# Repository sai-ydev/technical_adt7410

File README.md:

# ADT74x0 Technical Challenge

This repository contains the Python driver and the hardware design files meant for a take-home assignment offered by an organization. 

## Task Briefing

Your task is to create a thermostat that will also log temperature with a 10sec period. We've already chosen to integrate this into the Raspberry Pi CM4 system we are using, and to use the AD7414 temperature sensor chip. You are expected to create the electrical interface from the AD7414 to the Raspberry Pi and write the little bit of software to drive it.

The schematic has been started, and is provided for you as a kicad file, but really this is an exercise so feel completely free to return your answer as pen drawn on the PDF if that's easier. The pins GPIO0-GPIO13 are available to you, but I2C bus 0 has some devices on it already so do not use it so as to avoid contention for the bus. To the schematic, add 2 Watts of switchable heat, using a heating element of your choice. Make sure to specify it properly, either a part number if you're using something off the shelf, or construction details if making one from scratch. The heating element can be either board-mounted or attached by wires.

Write enough Python software to use this as a thermostat that can keep the temperature above a set point as well as log the temperature averaged over the last ten seconds, every ten seconds. Target Python 3.6 and write against the following API for board support.

## My Submission
 I used an ADT7420 temperature sensor. This was because AD7414 were generally not available from major distributors and I approached this problem as if I were actually designing a PCB for a real-life project. This repository includes the python drivers. 
 
 * `adt7420.py` - Drivers for the ADT7420 Temperature Sensor
 * `thermostat.py` - Thermostat class for interfacing temperature sensor and turn on heater

## Hardware

The Eagle PCB schematic and layout files are available in the `hardware` folder. It also includes a BOM file and Gerber files.

## Sources
1. My STM32 drivers for ADT7410 - [Link](https://github.com/sai-ydev/adt7410)
2. Analog ADT74x0 driver - [Link](https://github.com/analogdevicesinc/EVAL-ADICUP360/tree/master/projects/ADuCM360_demo_adt7420_pmdz)

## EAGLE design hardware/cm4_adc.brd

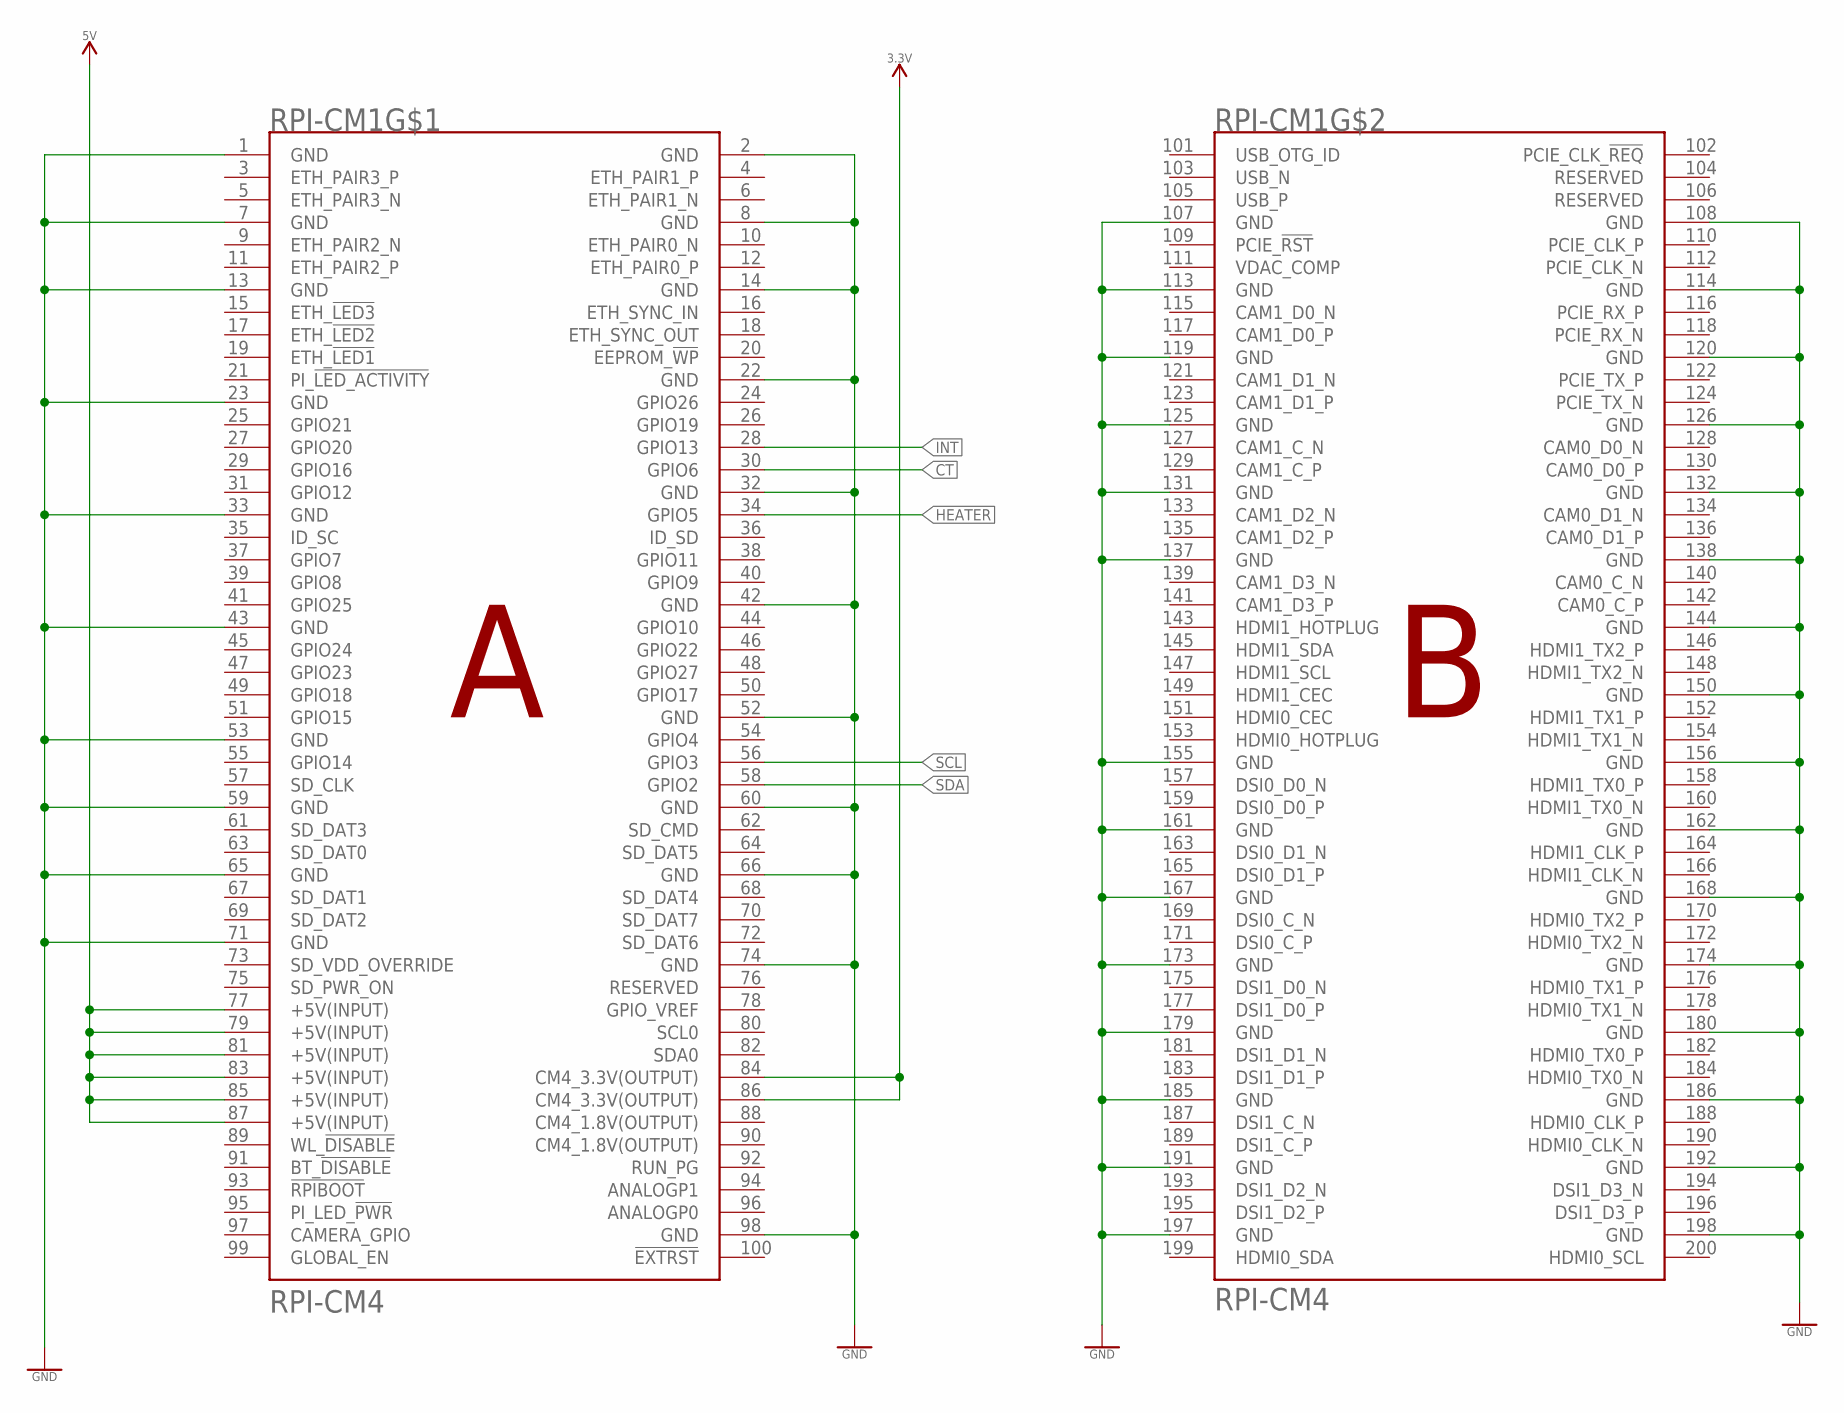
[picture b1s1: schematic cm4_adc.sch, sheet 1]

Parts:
RPI-CM1: RPI-CM4

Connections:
3.3V: RPI-CM1.84 (CM4_3.3V(OUTPUT)), RPI-CM1.86 (CM4_3.3V(OUTPUT)); also elsewhere on the board
5V: RPI-CM1.77 (+5V(INPUT)), RPI-CM1.79 (+5V(INPUT)), RPI-CM1.81 (+5V(INPUT)), RPI-CM1.83 (+5V(INPUT)), RPI-CM1.85 (+5V(INPUT)), RPI-CM1.87 (+5V(INPUT)); also elsewhere on the board
CT: RPI-CM1.30 (GPIO6); also elsewhere on the board
GND: RPI-CM1.1 (GND), RPI-CM1.2 (GND), RPI-CM1.7 (GND), RPI-CM1.8 (GND), RPI-CM1.13 (GND), RPI-CM1.14 (GND), RPI-CM1.22 (GND), RPI-CM1.23 (GND), RPI-CM1.32 (GND), RPI-CM1.33 (GND), RPI-CM1.42 (GND), RPI-CM1.43 (GND), RPI-CM1.52 (GND), RPI-CM1.53 (GND), RPI-CM1.59 (GND), RPI-CM1.60 (GND), RPI-CM1.65 (GND), RPI-CM1.66 (GND), RPI-CM1.71 (GND), RPI-CM1.74 (GND), RPI-CM1.98 (GND), RPI-CM1.107 (GND), RPI-CM1.108 (GND), RPI-CM1.113 (GND), RPI-CM1.114 (GND), RPI-CM1.119 (GND), RPI-CM1.120 (GND), RPI-CM1.125 (GND), RPI-CM1.126 (GND), RPI-CM1.131 (GND), RPI-CM1.132 (GND), RPI-CM1.137 (GND), RPI-CM1.138 (GND), RPI-CM1.144 (GND), RPI-CM1.150 (GND), RPI-CM1.155 (GND), RPI-CM1.156 (GND), RPI-CM1.161 (GND), RPI-CM1.162 (GND), RPI-CM1.167 (GND), RPI-CM1.168 (GND), RPI-CM1.173 (GND), RPI-CM1.174 (GND), RPI-CM1.179 (GND), RPI-CM1.180 (GND), RPI-CM1.185 (GND), RPI-CM1.186 (GND), RPI-CM1.191 (GND), RPI-CM1.192 (GND), RPI-CM1.197 (GND), RPI-CM1.198 (GND); also elsewhere on the board
HEATER: RPI-CM1.34 (GPIO5); also elsewhere on the board
INT: RPI-CM1.28 (GPIO13); also elsewhere on the board
SCL: RPI-CM1.56 (GPIO3); also elsewhere on the board
SDA: RPI-CM1.58 (GPIO2); also elsewhere on the board

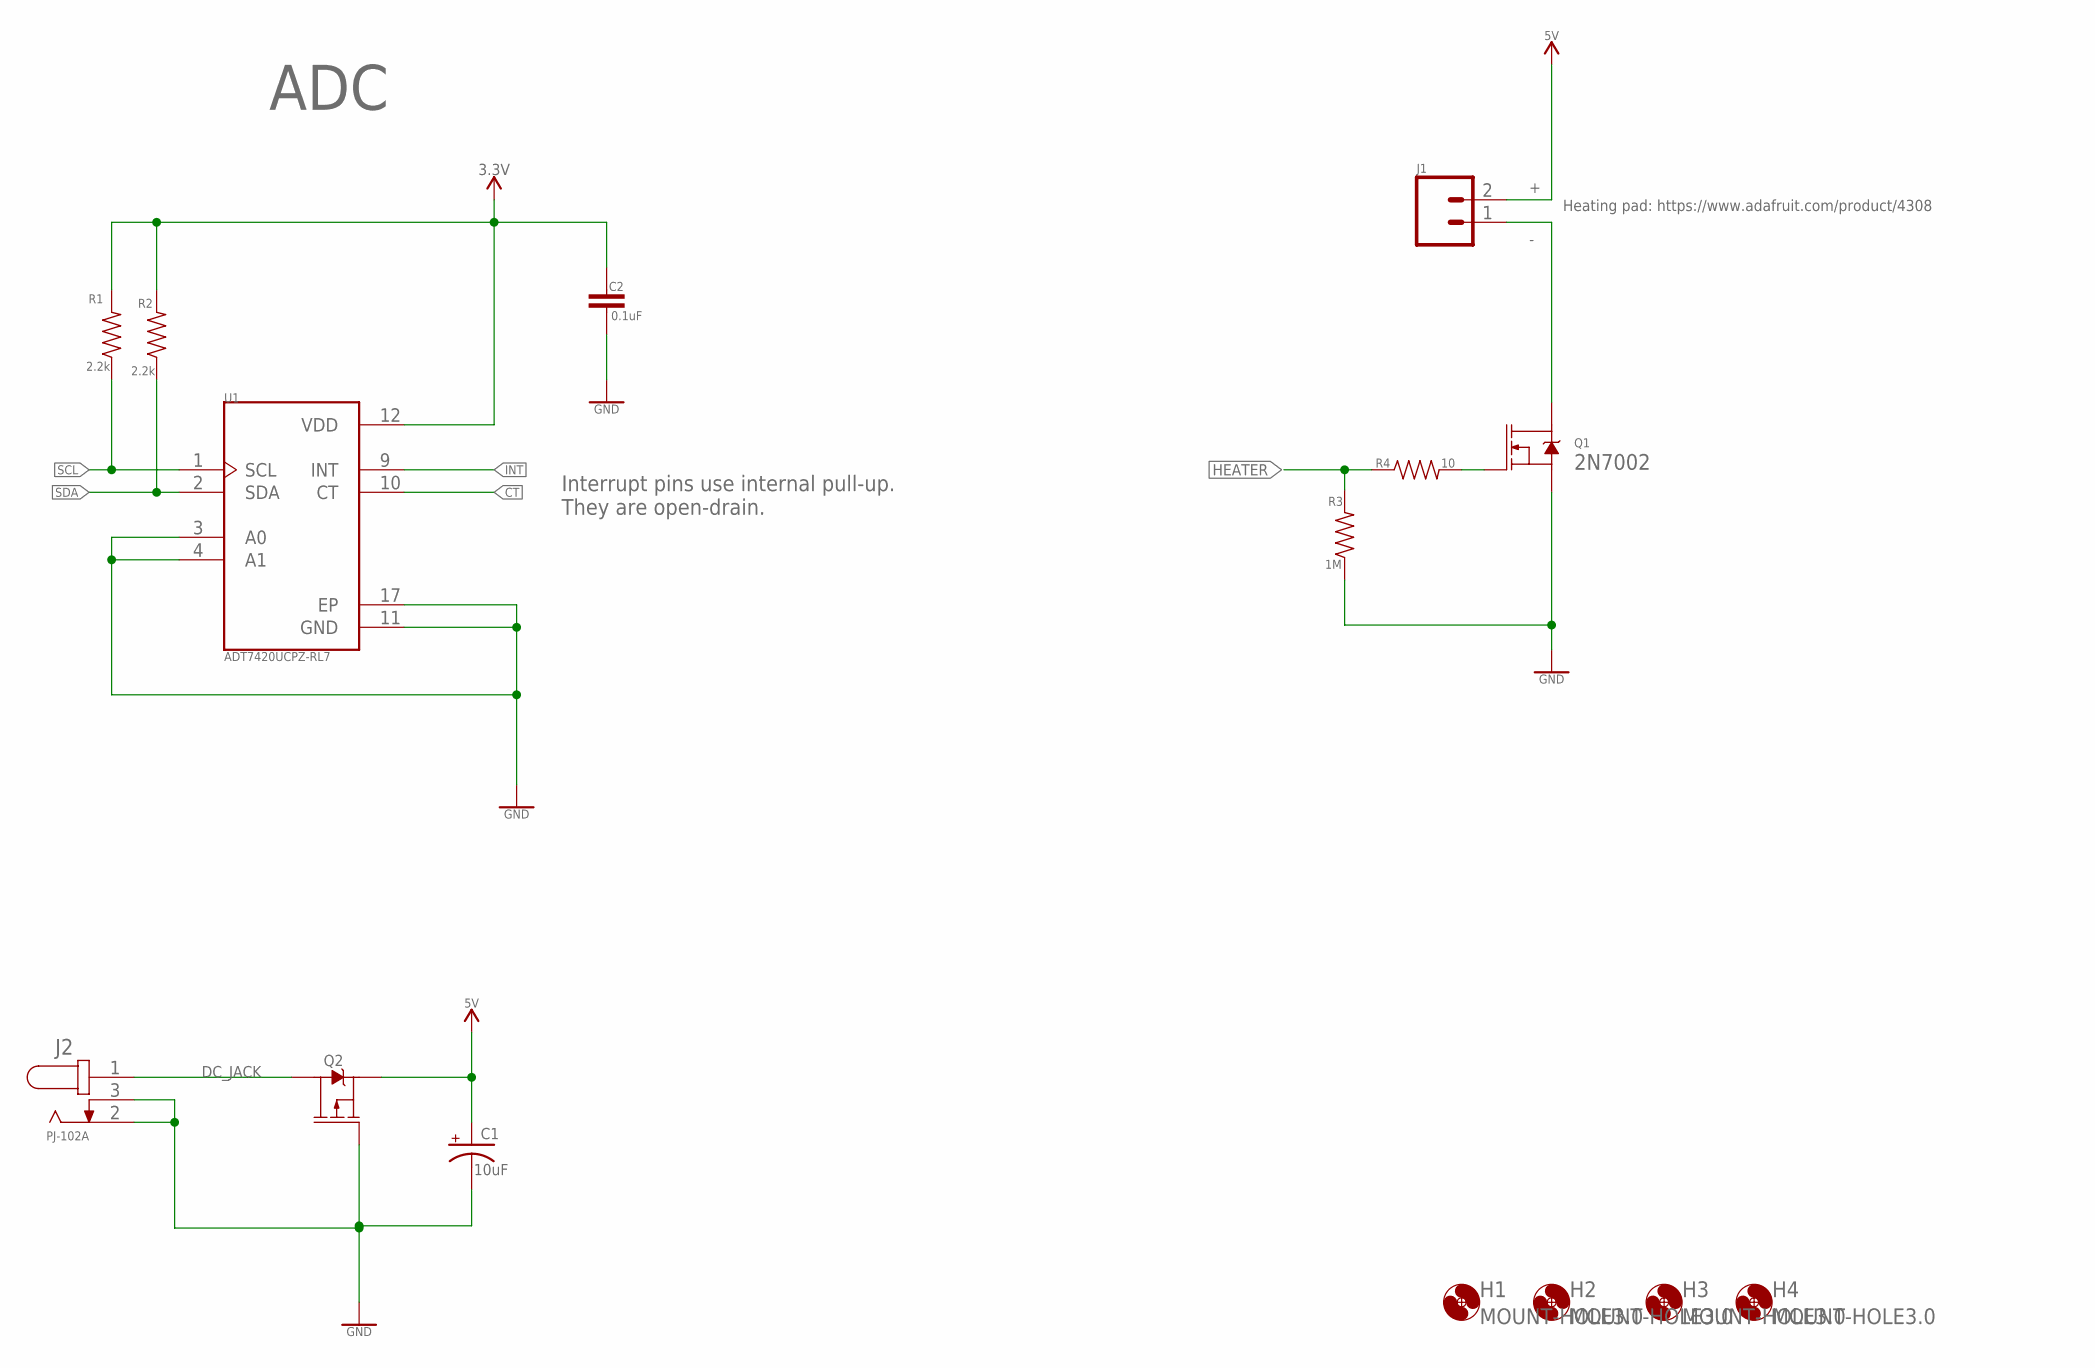
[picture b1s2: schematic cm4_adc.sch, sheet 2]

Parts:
C1: 10uF; EIA3216
C2: 0.1uF; 0603
H1, H2, H3, H4: MOUNT-HOLE3.0; 3,0
J1: CONN_023.5MM; SCREWTERMINAL-3.5MM-2
J2: PJ-102A; CUI_PJ-102A
Q1: 2N7002; SOT323
Q2: 2.5A/30V/105mΩ; SOT23-3
R1, R2: 2.2k; 0603
R3: 1M; 0603
R4: 10; 0603
U1: ADT7420UCPZ-RL7; QFN65P400X400X80-17N

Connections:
3.3V: C2.1, R1.2, R2.2, U1.12 (VDD); also elsewhere on the board
5V: C1.+, J1.2, Q2.2 (S); also elsewhere on the board
CT: U1.10 (CT); also elsewhere on the board
DC_JACK: J2.1, Q2.3 (D)
GND: C1.-, C2.2, J2.2, J2.3, Q1.2 (S), Q2.1 (G), R3.1, U1.3 (A0), U1.4 (A1), U1.11 (GND), U1.17 (EP); also elsewhere on the board
HEATER: R3.2, R4.1; also elsewhere on the board
INT: U1.9 (INT); also elsewhere on the board
unnamed: J1.1, Q1.3 (D)
unnamed: Q1.1 (G), R4.2
SCL: R1.1, U1.1 (SCL); also elsewhere on the board
SDA: R2.1, U1.2 (SDA); also elsewhere on the board

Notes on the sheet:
Interrupt pins use internal pull-up. They are open-drain.
ADC
Heating pad: https://www.adafruit.com/product/4308

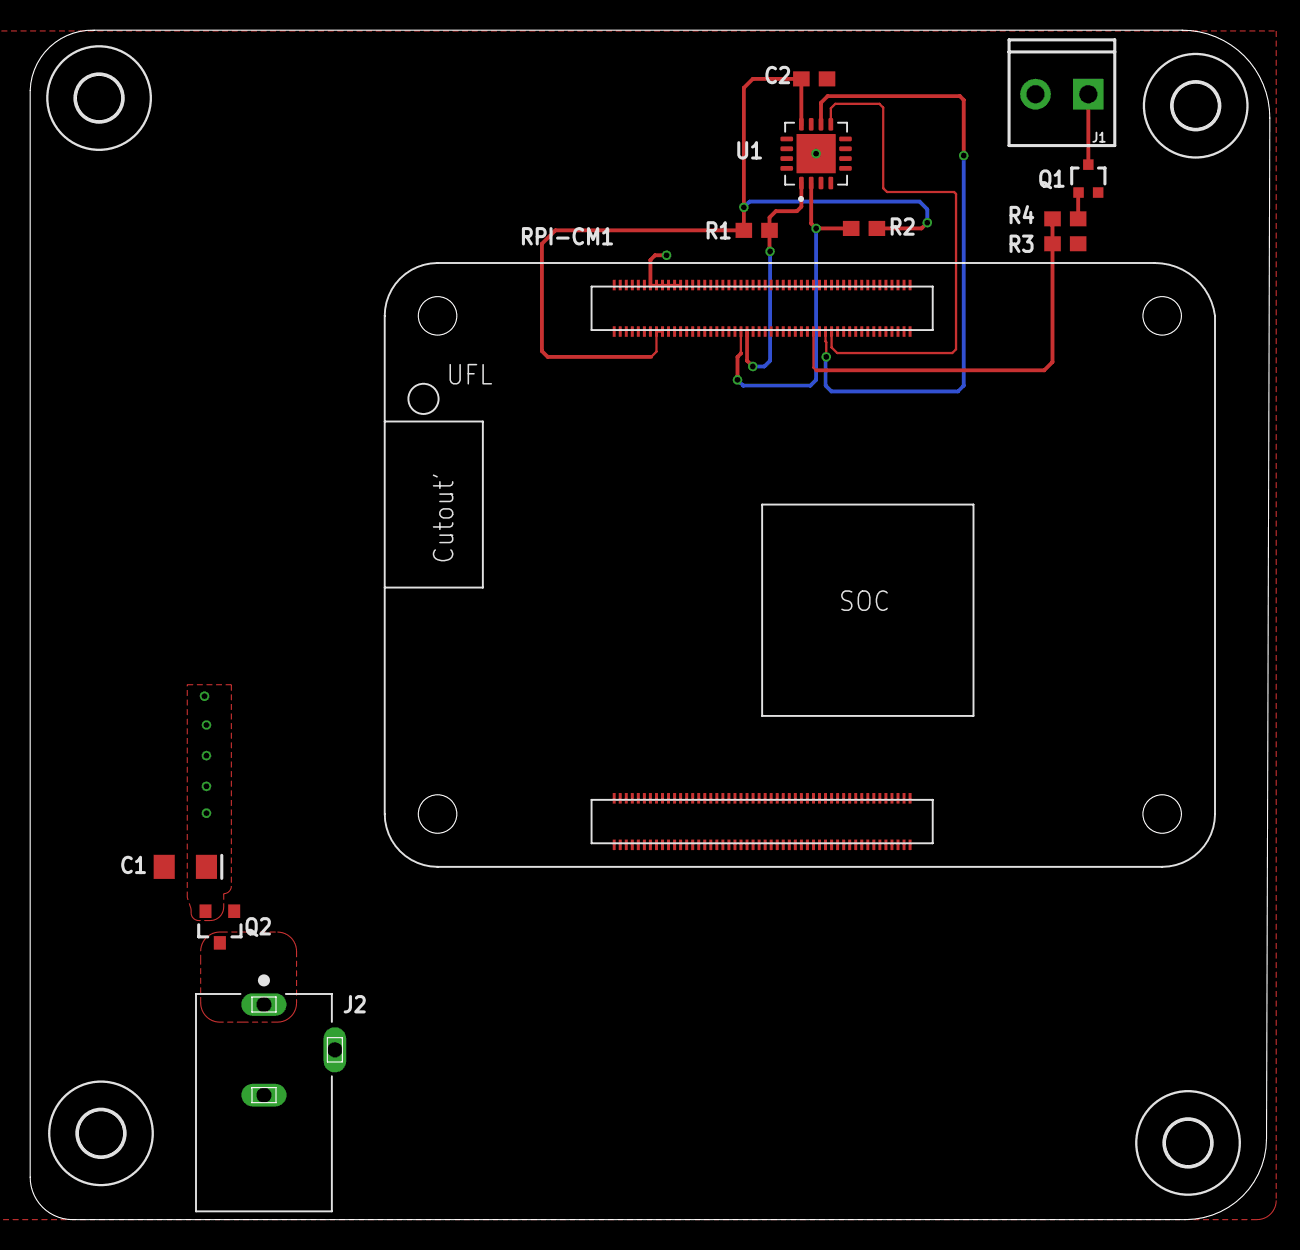
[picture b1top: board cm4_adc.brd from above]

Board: 2 copper layers, 82.1 x 78.8 mm, 16 parts (0 on the bottom side), 11 nets.

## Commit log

2022-03-11 check-in
2022-03-11 final submission
2022-03-14 Major file changes
    Changes to Schematic, Part number updates etc.
2022-03-14 Code cleanup
    cleaned up the temperature sensor and the thermostat
2022-03-14 Delete technical_submission.zip
    Removing first submission's zip file.
2022-03-14 Renaming gerber files
    Renamed it indicate they are gerbers.

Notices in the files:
parts and their libraries:
SparkFun-Resistors: Licensing: Creative Commons ShareAlike 4.0 International - https://creativecommons.org/licenses/by-sa/4.0
